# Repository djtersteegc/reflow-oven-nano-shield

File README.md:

# reflow-oven-nano-shield
ControLeo2 compatible reflow oven shield using an Arduino Nano

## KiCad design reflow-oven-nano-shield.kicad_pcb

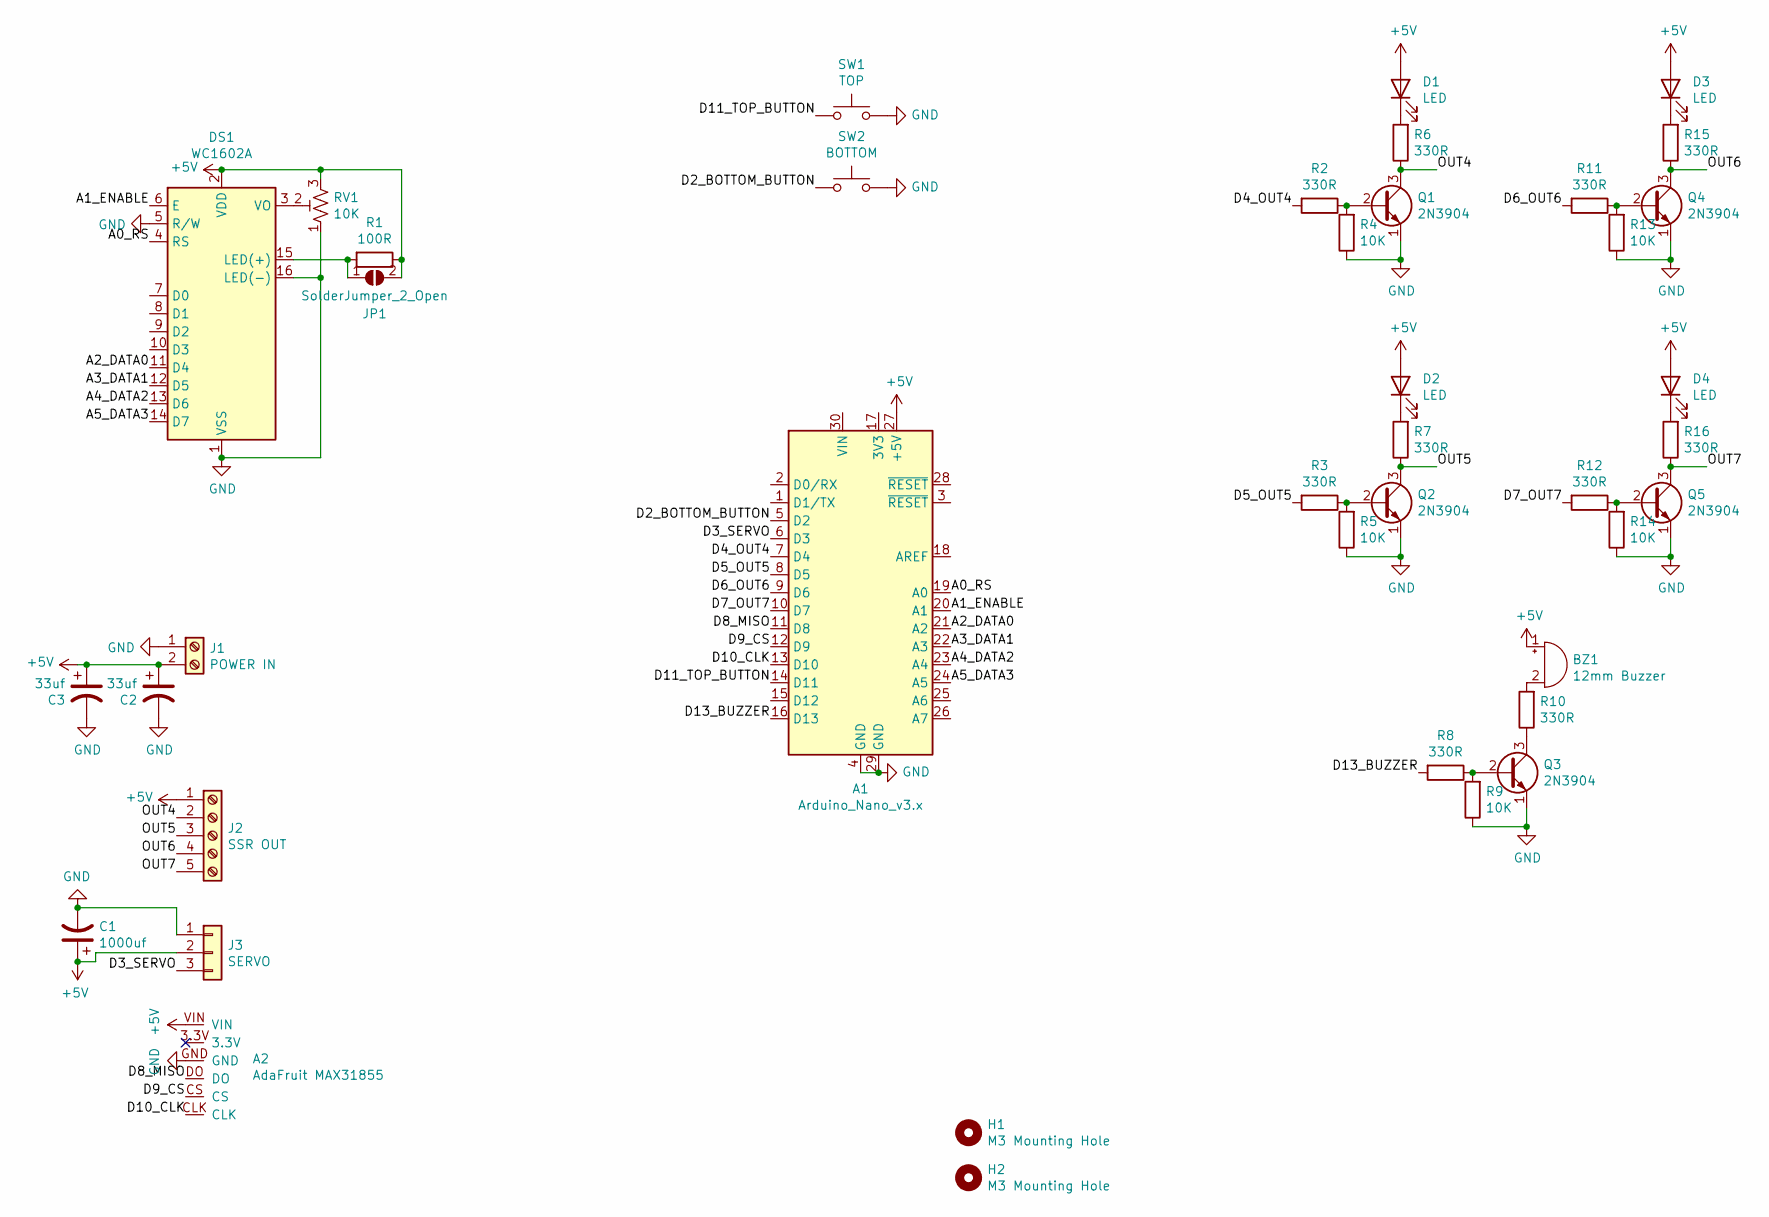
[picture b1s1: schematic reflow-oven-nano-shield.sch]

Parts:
A1: Arduino_Nano_v3.x; Arduino_Nano
A2: AdaFruit MAX31855; Adafruit Max31855
BZ1: 12mm Buzzer; Buzzer_12x9.5RM7.6
C1: 1000uf; CP_Radial_D8.0mm_P3.50mm
C2, C3: 33uf; CP_Radial_D5.0mm_P2.00mm
D1, D2, D3, D4: LED; LED_D5.0mm
DS1: WC1602A
H1, H2: M3 Mounting Hole; MountingHole_3.2mm_M3_Pad_Via
J1: POWER IN; TerminalBlock_Phoenix_MKDS-1,5-2-5.08_1x02_P5.08mm_Horizont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
J2: SSR OUT; TerminalBlock_Phoenix_MKDS-1,5-5-5.08_1x05_P5.08mm_Horizont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
J3: SERVO; PinHeader_1x03_P2.54mm_Horizontal
JP1: SolderJumper_2_Open; SolderJumper-2_P1.3mm_Open_TrianglePad1.0x1.5mm
Q1, Q2, Q3, Q4, Q5: 2N3904; TO-92_HandSolder
R1: 100R; R_Axial_DIN0207_L6.3mm_D2.5mm_P7.62mm_Horizontal
R2, R3, R6, R7, R8, R10, R11, R12, R15, R16: 330R; R_Axial_DIN0207_L6.3mm_D2.5mm_P7.62mm_Horizontal
R4, R5, R9, R13, R14: 10K; R_Axial_DIN0207_L6.3mm_D2.5mm_P7.62mm_Horizontal
RV1: 10K; TRIM_3362P-1-103
SW1: TOP; SW_PUSH_6mm_H4.3mm
SW2: BOTTOM; SW_PUSH_6mm_H4.3mm

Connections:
+5V: A1.27 (+5V), A2.VIN, BZ1.1 (-), C1.1, C2.1, C3.1, D1.2 (A), D2.2 (A), D3.2 (A), D4.2 (A), DS1.2 (VDD), J1.2, J2.1, J3.2, JP1.2 (B), R1.1, RV1.3
/A0_RS: A1.19 (A0), DS1.4 (RS)
/A1_ENABLE: A1.20 (A1), DS1.6 (E)
/A2_DATA0: A1.21 (A2), DS1.11 (D4)
/A3_DATA1: A1.22 (A3), DS1.12 (D5)
/A4_DATA2: A1.23 (A4), DS1.13 (D6)
/A5_DATA3: A1.24 (A5), DS1.14 (D7)
/D2_BOTTOM_BUTTON: A1.5 (D2), SW2.1
/D3_SERVO: A1.6 (D3), J3.3
/D4_OUT4: A1.7 (D4), R2.2
/D5_OUT5: A1.8 (D5), R3.2
/D6_OUT6: A1.9 (D6), R11.2
/D7_OUT7: A1.10 (D7), R12.2
/D8_MISO: A1.11 (D8), A2.DO
/D9_CS: A1.12 (D9), A2.CS
/D10_CLK: A1.13 (D10), A2.CLK
/D11_TOP_BUTTON: A1.14 (D11), SW1.1
/D13_BUZZER: A1.16 (D13), R8.2
/OUT4: J2.2, Q1.3 (C), R6.1
/OUT5: J2.3, Q2.3 (C), R7.1
/OUT6: J2.4, Q4.3 (C), R15.1
/OUT7: J2.5, Q5.3 (C), R16.1
GND: A1.4 (GND), A1.29 (GND), A2.GND, C1.2, C2.2, C3.2, DS1.1 (VSS), DS1.5 (R/W), DS1.16 (LED(-)), J1.1, J3.1, Q1.1 (E), Q2.1 (E), Q3.1 (E), Q4.1 (E), Q5.1 (E), R4.1, R5.1, R9.1, R13.1, R14.1, RV1.1, SW1.2, SW2.2
unnamed: BZ1.2 (+), R10.2
unnamed: D1.1 (K), R6.2
unnamed: D2.1 (K), R7.2
unnamed: D3.1 (K), R15.2
unnamed: D4.1 (K), R16.2
unnamed: DS1.3 (VO), RV1.2
unnamed: DS1.15 (LED(+)), JP1.1 (A), R1.2
unnamed: Q1.2 (B), R2.1, R4.2
unnamed: Q2.2 (B), R3.1, R5.2
unnamed: Q3.2 (B), R8.1, R9.2
unnamed: Q3.3 (C), R10.1
unnamed: Q4.2 (B), R11.1, R13.2
unnamed: Q5.2 (B), R12.1, R14.2

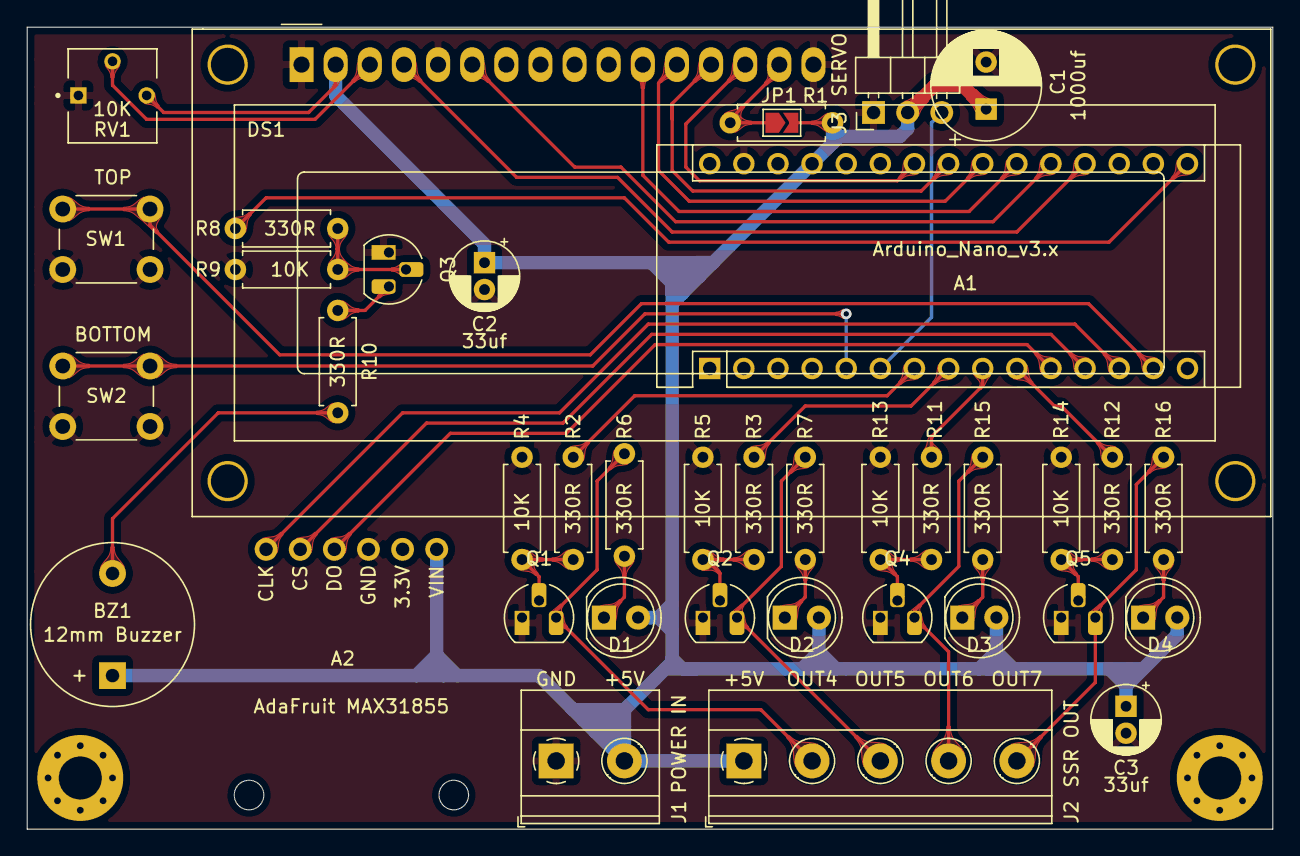
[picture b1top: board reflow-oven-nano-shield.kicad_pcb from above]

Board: 2 copper layers, 92.7 x 59.7 mm, 41 parts (0 on the bottom side), 36 nets.

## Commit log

2022-04-17 Hand solder TO-92 footprint, add teardrops
